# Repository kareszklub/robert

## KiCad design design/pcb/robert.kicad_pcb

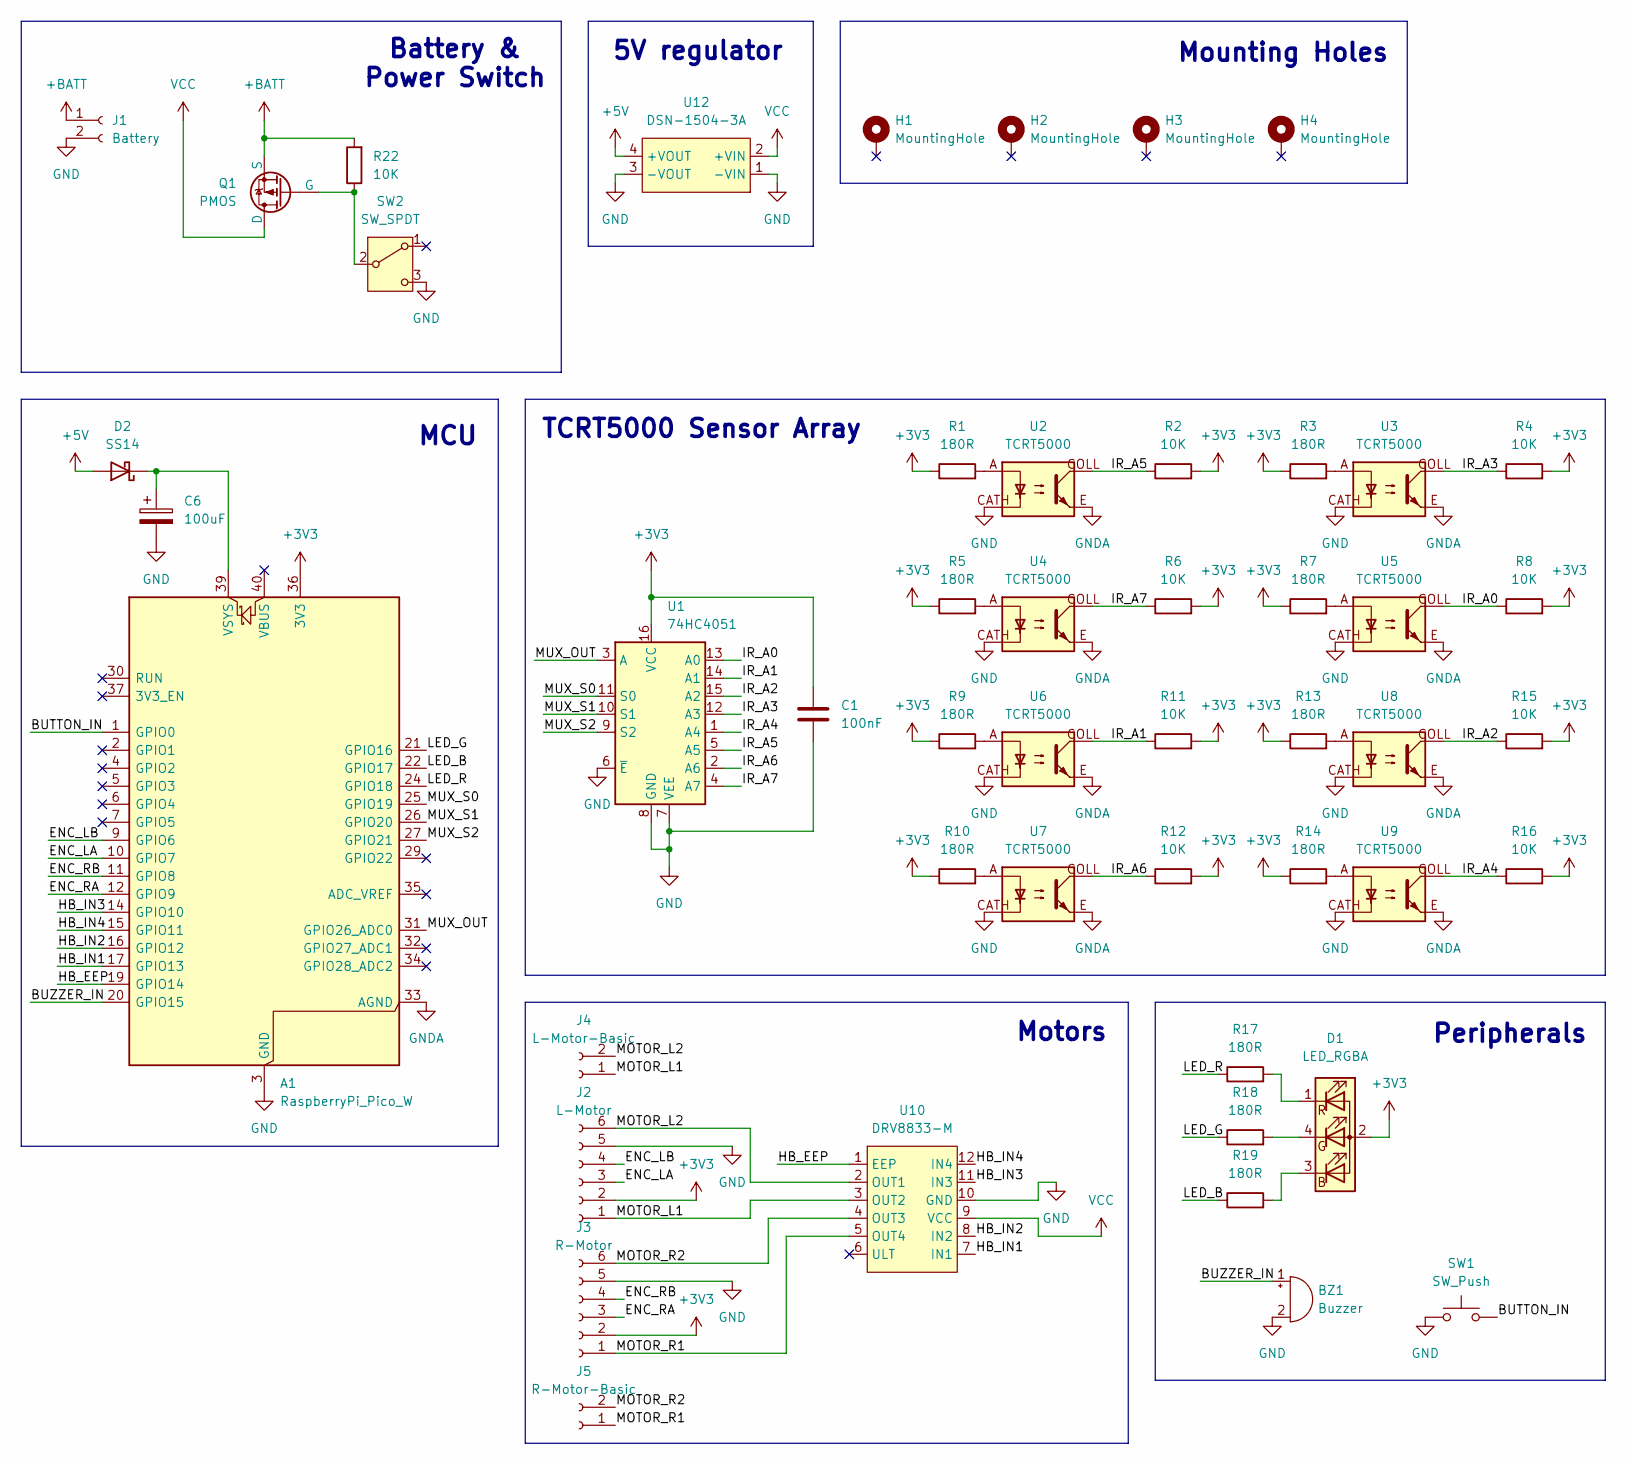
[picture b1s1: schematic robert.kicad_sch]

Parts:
A1: RaspberryPi_Pico_W; RaspberryPi_Pico_Common_THT
BZ1: Buzzer; Buzzer_TDK_PS1240P02BT_D12.2mm_H6.5mm
C1: 100nF; C_1206_3216Metric_Pad1.33x1.80mm_HandSolder
C6: 100uF; CP_Radial_D5.0mm_P2.00mm
D1: LED_RGBA; LED_D5.0mm-4_RGB
D2: SS14; D_SMA_Handsoldering
H1, H2, H3, H4: MountingHole; MountingHole_2.7mm_M2.5_DIN965_Pad
J1: Battery; JST_XH_B2B-XH-A_1x02_P2.50mm_Vertical
J2: L-Motor; JST_XH_B6B-XH-A_1x06_P2.50mm_Vertical
J3: R-Motor; JST_XH_B6B-XH-A_1x06_P2.50mm_Vertical
J4: L-Motor-Basic; JST_XH_B2B-XH-A_1x02_P2.50mm_Vertical
J5: R-Motor-Basic; JST_XH_B2B-XH-A_1x02_P2.50mm_Vertical
Q1: PMOS; TSOT-23_HandSoldering
R1, R3, R5, R7, R9, R10, R13, R14, R17, R18, R19: 180R; R_1206_3216Metric_Pad1.30x1.75mm_HandSolder
R2, R4, R6, R8, R11, R12, R15, R16, R22: 10K; R_1206_3216Metric_Pad1.30x1.75mm_HandSolder
SW1: SW_Push; SW_PUSH_6mm
SW2: SW_SPDT; PinHeader_1x03_P2.54mm_Vertical
U1: 74HC4051; DIP-16_W7.62mm
U2, U3, U4, U5, U6, U7, U8, U9: TCRT5000; tcrt5000
U10: DRV8833-M; DRV8833 Motor driver module
U12: DSN-1504-3A; DSN-1504 step-down module

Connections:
+3V3: A1.36 (3V3), C1.1, D1.2 (A), J2.2, J3.2, R1.1, R2.2, R3.1, R4.2, R5.1, R6.2, R7.1, R8.2, R9.1, R10.1, R11.2, R12.2, R13.1, R14.1, R15.2, R16.2, U1.16 (VCC)
+5V: D2.2 (A), U12.4 (+VOUT)
+BATT: J1.1, Q1.3 (S), R22.2
/BUTTON_IN: A1.1 (GPIO0), SW1.2
/BUZZER_IN: A1.20 (GPIO15), BZ1.1 (+)
/ENC_LA: A1.10 (GPIO7), J2.3
/ENC_LB: A1.9 (GPIO6), J2.4
/ENC_RA: A1.12 (GPIO9), J3.3
/ENC_RB: A1.11 (GPIO8), J3.4
/HB_EEP: A1.19 (GPIO14), U10.1 (EEP)
/HB_IN1: A1.17 (GPIO13), U10.7 (IN1)
/HB_IN2: A1.16 (GPIO12), U10.8 (IN2)
/HB_IN3: A1.14 (GPIO10), U10.11 (IN3)
/HB_IN4: A1.15 (GPIO11), U10.12 (IN4)
/IR_A0: R8.1, U1.13 (A0), U5.COLL
/IR_A1: R11.1, U1.14 (A1), U6.COLL
/IR_A2: R15.1, U1.15 (A2), U8.COLL
/IR_A3: R4.1, U1.12 (A3), U3.COLL
/IR_A4: R16.1, U1.1 (A4), U9.COLL
/IR_A5: R2.1, U1.5 (A5), U2.COLL
/IR_A6: R12.1, U1.2 (A6), U7.COLL
/IR_A7: R6.1, U1.4 (A7), U4.COLL
/LED_B: A1.22 (GPIO17), R19.1
/LED_G: A1.21 (GPIO16), R18.1
/LED_R: A1.24 (GPIO18), R17.1
/MOTOR_L1: J2.1, J4.1, U10.3 (OUT2)
/MOTOR_L2: J2.6, J4.2, U10.2 (OUT1)
/MOTOR_R1: J3.1, J5.1, U10.5 (OUT4)
/MOTOR_R2: J3.6, J5.2, U10.4 (OUT3)
/MUX_OUT: A1.31 (GPIO26_ADC0), U1.3 (A)
/MUX_S0: A1.25 (GPIO19), U1.11 (S0)
/MUX_S1: A1.26 (GPIO20), U1.10 (S1)
/MUX_S2: A1.27 (GPIO21), U1.9 (S2)
GND: A1.3 (GND), A1.8 (GND), A1.13 (GND), A1.18 (GND), A1.23 (GND), A1.28 (GND), A1.38 (GND), BZ1.2 (-), C1.2, C6.2, J1.2, J2.5, J3.5, SW1.1, SW2.3 (C), U1.6 (~E), U1.7 (VEE), U1.8 (GND), U2.CATH, U3.CATH, U4.CATH, U5.CATH, U6.CATH, U7.CATH, U8.CATH, U9.CATH, U10.10 (GND), U12.1 (-VIN), U12.3 (-VOUT)
GNDA: A1.33 (AGND), U2.E, U3.E, U4.E, U5.E, U6.E, U7.E, U8.E, U9.E
unnamed: A1.39 (VSYS), C6.1, D2.1 (K)
unnamed: D1.3 (BK), R19.2
unnamed: D1.4 (GK), R18.2
unnamed: D1.1 (RK), R17.2
unnamed: Q1.2 (G), R22.1, SW2.2 (B)
unnamed: R1.2, U2.A
unnamed: R3.2, U3.A
unnamed: R5.2, U4.A
unnamed: R7.2, U5.A
unnamed: R9.2, U6.A
unnamed: R10.2, U7.A
unnamed: R13.2, U8.A
unnamed: R14.2, U9.A
VCC: Q1.1 (D), U10.9 (VCC), U12.2 (+VIN)

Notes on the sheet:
5V regulator
TCRT5000 Sensor Array
Peripherals
Motors
MCU
Battery & Power Switch
Mounting Holes

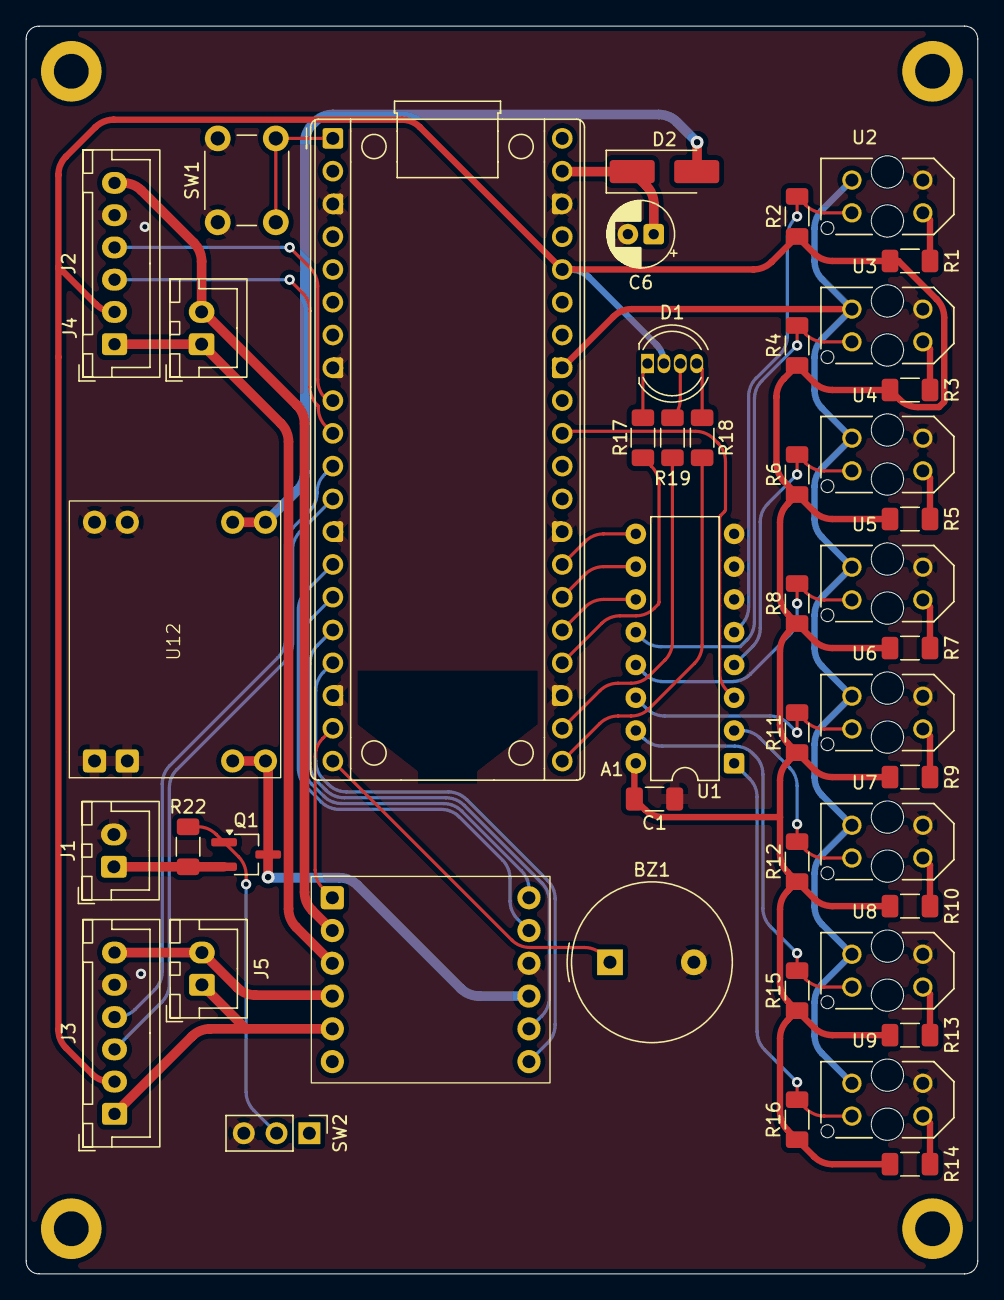
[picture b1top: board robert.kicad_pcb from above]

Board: 2 copper layers, 73.8 x 96.7 mm, 49 parts (0 on the bottom side), 49 nets.

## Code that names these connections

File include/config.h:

#pragma once

#include <pico/types.h>

namespace config {

constexpr uint BUTTON_PIN = 0;

constexpr uint BUZZER_PIN = 14;

constexpr uint RGB_LED_R_PIN = 18;
constexpr uint RGB_LED_G_PIN = 19;
constexpr uint RGB_LED_B_PIN = 20;

constexpr uint HB_LA_PIN = 12;
constexpr uint HB_LB_PIN = 13;
constexpr uint HB_RA_PIN = 10;
constexpr uint HB_RB_PIN = 11;

constexpr uint ENC_LA_PIN = 6;
constexpr uint ENC_LB_PIN = 7;
constexpr uint ENC_RA_PIN = 8;
constexpr uint ENC_RB_PIN = 9;

constexpr float SC_PID_KP = 400;
constexpr float SC_PID_KI = 3500;
constexpr float SC_PID_KD = 0;
constexpr float SC_PID_INT_MIN = -45000;
constexpr float SC_PID_INT_MAX = 45000;

constexpr uint TRACK_LEFT_PIN = 28;
constexpr uint TRACK_RIGHT_PIN = 16;

constexpr uint SERVO_PIN = 22;
constexpr uint SERVO_MIN = 2100;
constexpr uint SERVO_MID = 4800;
constexpr uint SERVO_MAX = 8300;

constexpr uint ULTRA_TRIG_PIN = 27;
constexpr uint ULTRA_ECHO_PIN = 26;

} // namespace config

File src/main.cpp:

#include <pico/cyw43_arch.h>
#include <cstdio>
#include "h_bridge.h"
#include "hardware/adc.h"
#include "onboard_led.h"
#include "pico/stdlib.h"
#include "track_sensor.h"

#define IR_SENSOR_PIN 26
#define IR_SENSOR_ADC_CHAN 0
#define MUX_S0_PIN 21
#define MUX_S1_PIN 20
#define MUX_S2_PIN 19

int main() {
    stdio_init_all();
    adc_init();
    cyw43_arch_init();

    // TODO: This class has been implemented for a 7-sensor prototype, so this needs to be updated
    TrackSensor track(IR_SENSOR_PIN, IR_SENSOR_ADC_CHAN, MUX_S0_PIN, MUX_S1_PIN, MUX_S2_PIN);
    Pin button(0, Pin::Direction::In, Pin::Pull::Up);
    OnboardLed led;
    HBridge hb(13, 12, 10, 11);

    // TODO: HBridge sleep pin, this should be a member of the HBridge class
    Pin eep(14);
    eep.value(1);

    // hb.drive(0xffff, 0xffff);

    // This section performs a sensor calibrating sequence
    // ----------------------------------- //
    while (button.value())
        sleep_ms(10);

    led.on();
    for (int i = 0; i < 3000; i++) {
        track.update_bounds();
        sleep_ms(1);
    }
    led.off();
    // ----------------------------------- //

    while (true) {
        float data = track.read();
        printf("%2.4f\n", data);
        sleep_ms(10);
    }
}
